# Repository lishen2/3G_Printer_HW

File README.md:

# 3G_Printer_HW
secret project

Standalone not finished, may contain issues use with caution

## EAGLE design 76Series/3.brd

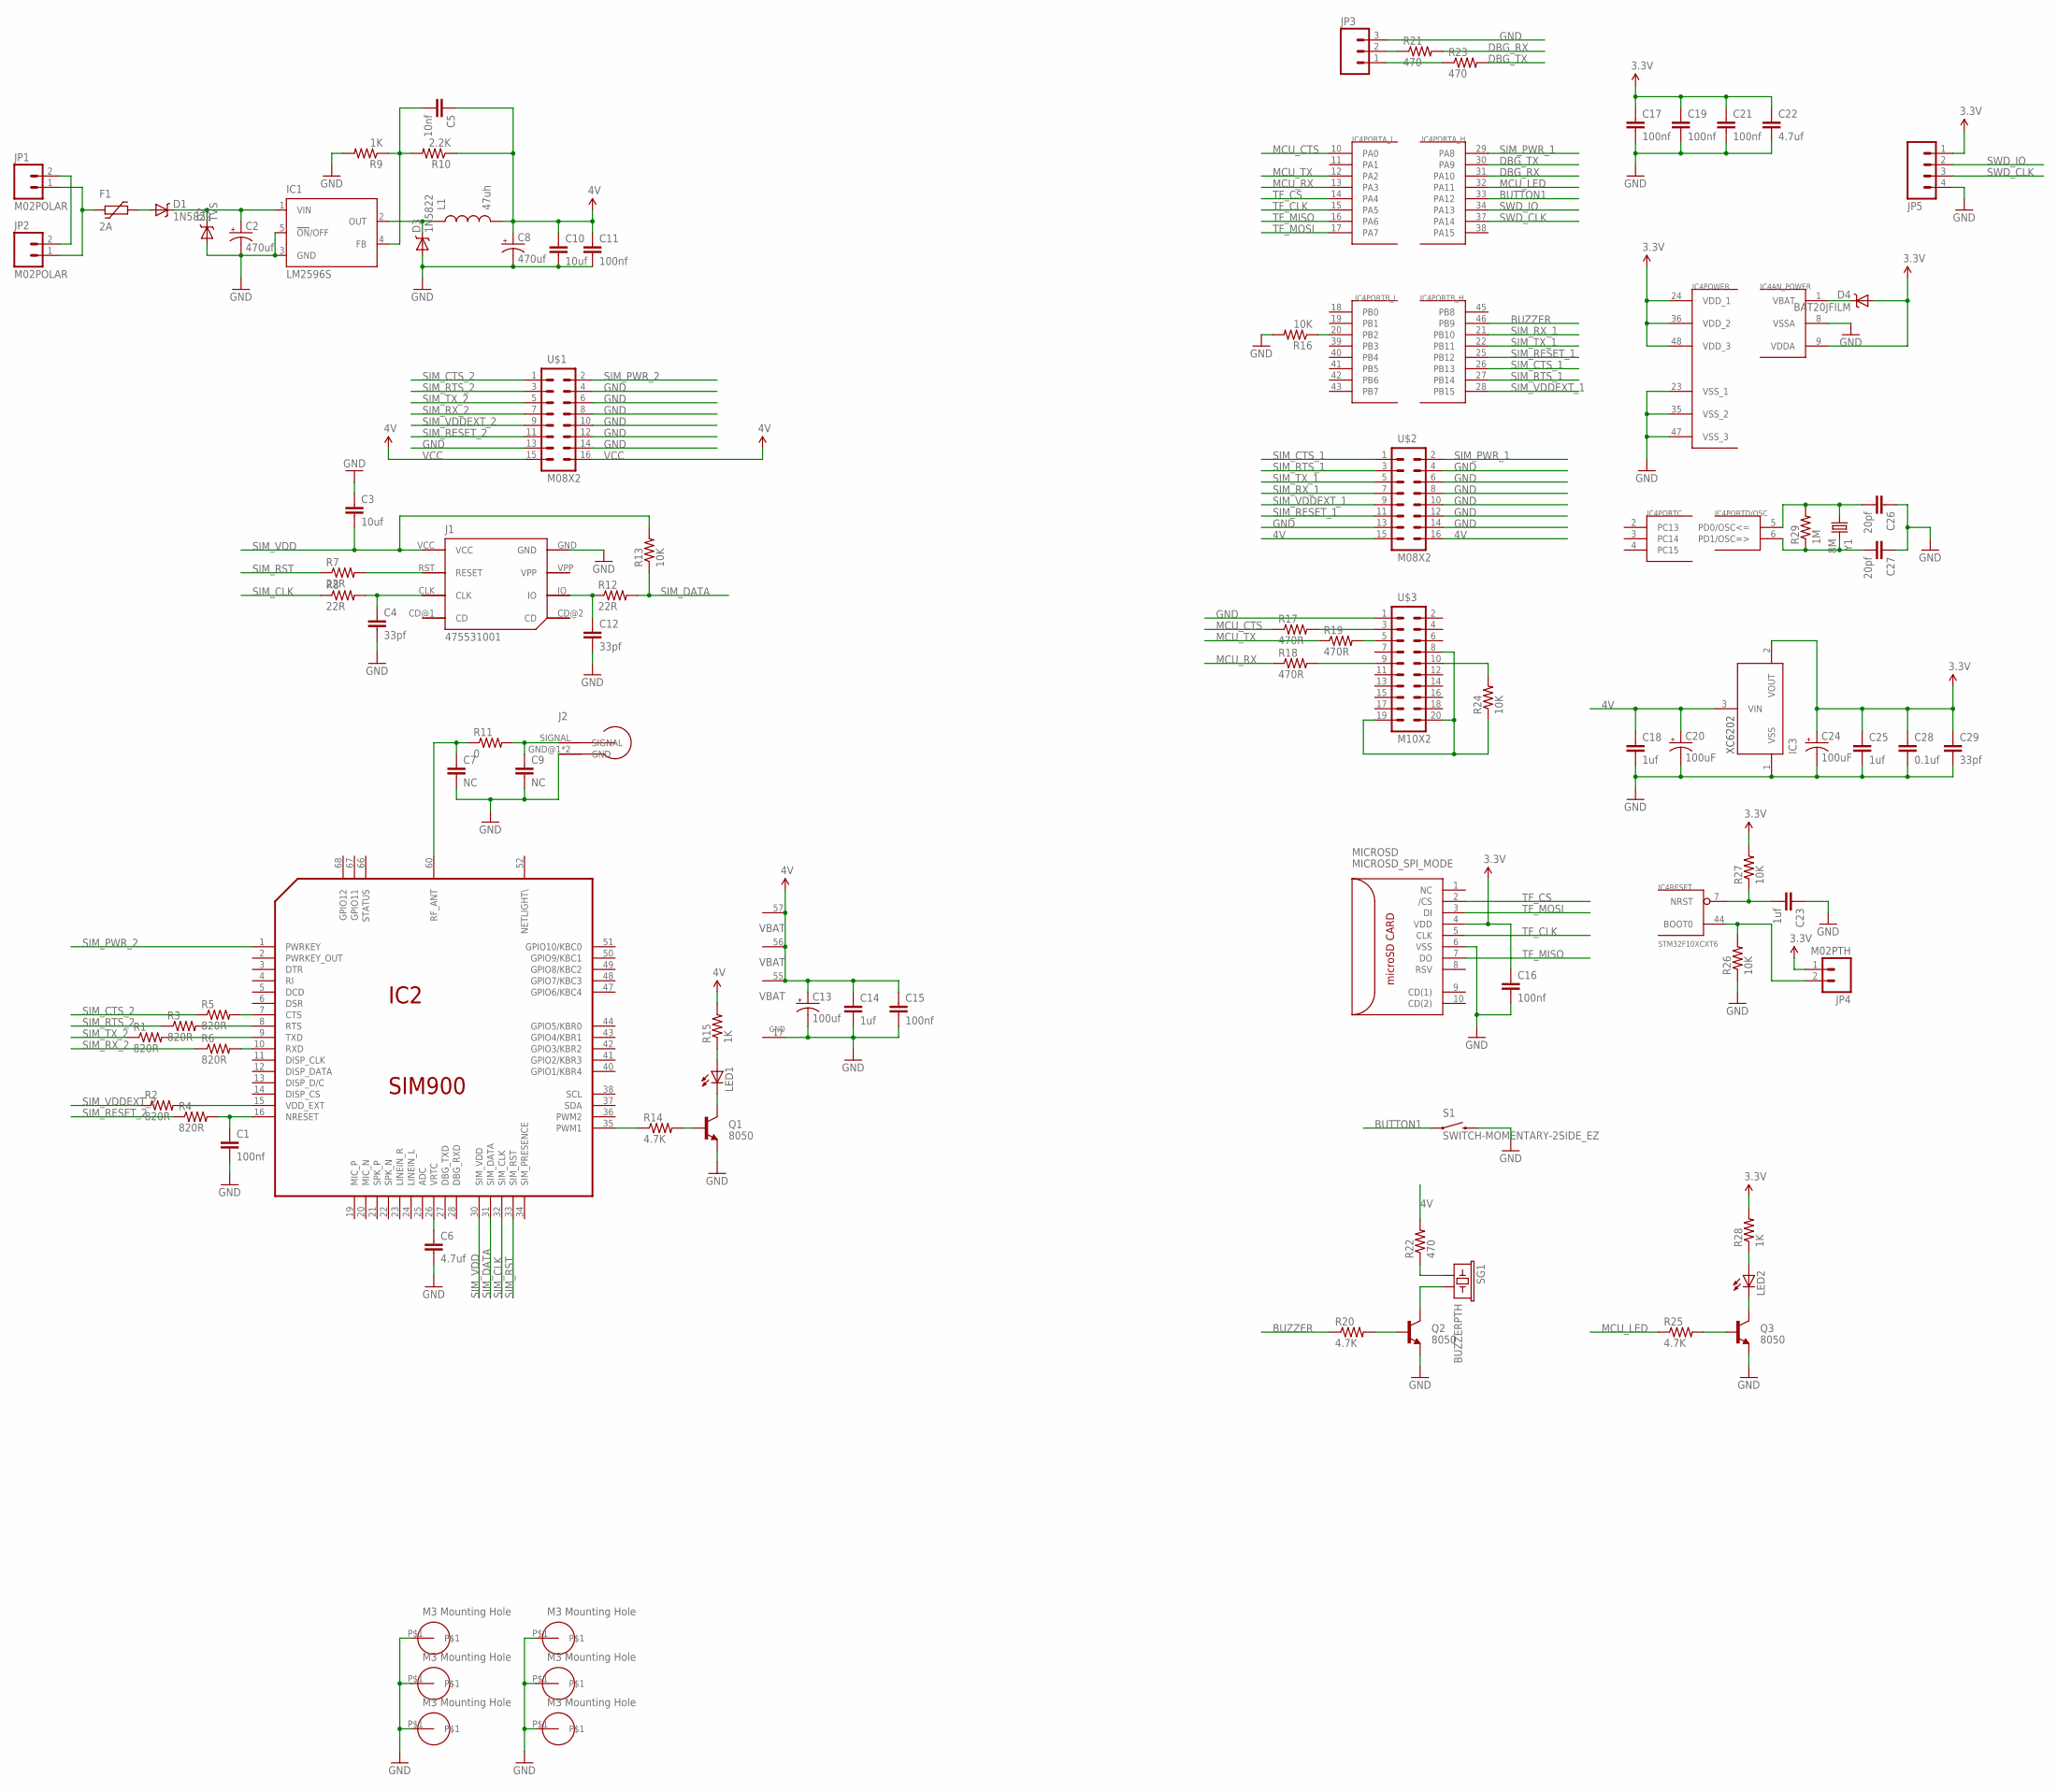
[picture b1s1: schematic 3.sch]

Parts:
C1, C11, C15, C16, C17, C19, C21: 100nf; 0603-CAP
C2: 470uf; CPOL-RADIAL-1000UF-25V
C3, C10: 10uf; 0603-CAP
C4, C12, C29: 33pf; 0603-CAP
C5: 10nf; 0603-CAP
C6, C22: 4.7uf; 0603-CAP
C7, C9: NC; 0603-CAP
C8: 470uf; PANASONIC_G
C13: 100uf; EIA6032
C14, C18, C23, C25: 1uf; 0603-CAP
C20, C24: 100uF; EIA3528
C26, C27: 20pf; 0603-CAP
C28: 0.1uf; 0603-CAP
D1, D3: 1N5822; SMB-DIODE
D2: TVS; SMB-DIODE
D4: BAT20JFILM; SOD-323
F1: 2A; 1812L
IC1: LM2596S; TO263-5
IC2: SIM900
IC3: XC6202; SOT23-3
IC4: STM32F10XCXT6; TQFP48
J1: 475531001
J2: IPEX
JP1, JP2: M02POLAR; MOLEX-1X2
JP3: M03PTH; 1X03
JP4: M02PTH; 1X02
JP5: M04PTH; 1X04
L1: 47uh; IHLP4040DZ
LED1: LEDSML0805; SML0805
LED2: LED3MM
MICROSD: MICROSD_SPI_MODE; MICRO_SD_CONNECTOR
Q1, Q2, Q3: 8050; SOT23
R1, R2, R3, R4, R5, R6: 820R; 0603-RES
R7, R8, R12: 22R; 0603-RES
R9, R15, R28: 1K; 0603-RES
R10: 2.2K; 0603-RES
R11: 0; 0603-RES
R13, R16, R24, R26, R27: 10K; 0603-RES
R14, R20, R25: 4.7K; 0603-RES
R17, R18, R19: 470R; 0603-RES
R21, R22, R23: 470; 0603-RES
R29: 1M; 0603-RES
S1: SWITCH-MOMENTARY-2SIDE_EZ; TACTILE-PTH-SIDEEZ
SG1: BUZZERPTH; BUZZER-12MM
U$1, U$2: M08X2; 2X8
U$3: M10X2; 2X10
U$4, U$5, U$7, U$8, U$10, U$11: M3_MOUNTING_HOLE
Y1: 8M; HC49US

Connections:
3.3V: C16.1, C17.1, C19.1, C21.1, C22.1, C24.A (+), C25.1, C28.1, C29.1, D4.2 (A), IC3.2 (VOUT), IC4.9 (VDDA), IC4.24 (VDD_1), IC4.36 (VDD_2), IC4.48 (VDD_3), JP4.1, JP5.1, MICROSD.4 (VDD), R27.2, R28.2
4V: C18.1, C20.A (+), IC3.3 (VIN), R22.2, U$2.15, U$2.16
BUTTON1: IC4.33 (PA12), S1.1
BUZZER: IC4.46 (PB9), R20.1
DBG_RX: IC4.31 (PA10), R21.2
DBG_TX: IC4.30 (PA9), R23.2
GND: C1.2, C2.2 (-), C3.1, C4.2, C6.2, C7.2, C8.-, C9.2, C10.2, C11.2, C12.2, C13.P$2 (-), C14.2, C15.2, C16.2, C17.2, C18.2, C19.2, C20.C (-), C21.2, C22.2, C23.1, C24.C (-), C25.2, C26.1, C27.1, C28.2, C29.2, D2.A, D3.A, IC1.3 (GND), IC1.5 (!ON!/OFF), IC2.17 (GND), IC2.18 (GND), IC2.29 (GND), IC2.39 (GND), IC2.45 (GND), IC2.46 (GND), IC2.53 (GND), IC2.54 (GND), IC2.58 (GND), IC2.59 (GND), IC2.61 (GND), IC2.62 (GND), IC2.63 (GND), IC2.64 (GND), IC2.65 (GND), IC3.1 (VSS), IC4.8 (VSSA), IC4.23 (VSS_1), IC4.35 (VSS_2), IC4.47 (VSS_3), J1.GND, J2.GND@1 (GND), J2.GND@2 (GND), JP3.3, JP5.4, MICROSD.6 (VSS), Q1.2 (E), Q2.2 (E), Q3.2 (E), R9.2, R16.2, R26.1, S1.2, U$1.4, U$1.6, U$1.8, U$1.10, U$1.12, U$1.13, U$1.14, U$2.4, U$2.6, U$2.8, U$2.10, U$2.12, U$2.13, U$2.14, U$3.1, U$4.P$1, U$5.P$1, U$7.P$1, U$8.P$1, U$10.P$1, U$11.P$1
MCU_CTS: IC4.10 (PA0), R17.1
MCU_LED: IC4.32 (PA11), R25.1
MCU_RX: IC4.13 (PA3), R18.1
MCU_TX: IC4.12 (PA2), R19.1
unnamed: D4.1 (C), IC4.1 (VBAT)
unnamed: C26.2, IC4.5 (PD0/OSC<=), R29.2, Y1.1
unnamed: C27.2, IC4.6 (PD1/OSC=>), R29.1, Y1.2
unnamed: C23.2, IC4.7 (NRST), R27.1
unnamed: IC4.44 (BOOT0), JP4.2, R26.2
unnamed: R24.1, U$3.8, U$3.19, U$3.20
unnamed: JP1.2, JP2.2
unnamed: D3.C, IC1.2 (OUT), L1.P$1 (1)
unnamed: C2.1 (+), D1.C, D2.C, IC1.1 (VIN)
unnamed: F1.P$1 (1), JP1.1, JP2.1
unnamed: C5.2, IC1.4 (FB), R9.1, R10.2
unnamed: R17.2, U$3.3
unnamed: R19.2, U$3.5
unnamed: LED1.C, Q1.3 (C)
unnamed: R24.2, U$3.10
unnamed: C7.1, IC2.60 (RF_ANT), R11.1
unnamed: IC4.20 (PB2), R16.1
unnamed: C9.1, J2.SIGNAL, R11.2
unnamed: D1.A, F1.P$2 (2)
unnamed: IC2.15 (VDD_EXT), R2.2
unnamed: IC2.35 (PWM1), R14.1
unnamed: Q1.1 (B), R14.2
unnamed: LED1.A, R15.1
unnamed: J1.RST (RESET), R7.2
unnamed: C6.1, IC2.26 (VRTC)
unnamed: Q3.1 (B), R25.2
unnamed: C1.1, IC2.16 (NRESET), R4.2
unnamed: IC2.7 (CTS), R5.2
unnamed: IC2.8 (RTS), R3.2
unnamed: IC2.9 (TXD), R1.2
unnamed: C12.1, J1.IO, R12.1
unnamed: IC2.10 (RXD), R6.2
unnamed: JP3.2, R21.1
unnamed: JP3.1, R23.1
unnamed: C4.1, J1.CLK, R8.2
unnamed: Q2.1 (B), R20.2
unnamed: R22.1, SG1.+ (1)
unnamed: Q2.3 (C), SG1.- (2)
unnamed: R18.2, U$3.9
unnamed: LED2.A, R28.1
unnamed: LED2.K (C), Q3.3 (C)
SIM_CLK: IC2.32 (SIM_CLK), R8.1
SIM_CTS_1: IC4.26 (PB13), U$2.1
SIM_CTS_2: R5.1, U$1.1
SIM_DATA: IC2.31 (SIM_DATA), R12.2, R13.1
SIM_PWR_1: IC4.29 (PA8), U$2.2
SIM_PWR_2: IC2.1 (PWRKEY), U$1.2
SIM_RESET_1: IC4.25 (PB12), U$2.11
SIM_RESET_2: R4.1, U$1.11
SIM_RST: IC2.33 (SIM_RST), R7.1
SIM_RTS_1: IC4.27 (PB14), U$2.3
SIM_RTS_2: R3.1, U$1.3
SIM_RX_1: IC4.21 (PB10), U$2.7
SIM_RX_2: R6.1, U$1.7
SIM_TX_1: IC4.22 (PB11), U$2.5
SIM_TX_2: R1.1, U$1.5
SIM_VDD: C3.2, IC2.30 (SIM_VDD), J1.VCC, R13.2
SIM_VDDEXT_1: IC4.28 (PB15), U$2.9
SIM_VDDEXT_2: R2.1, U$1.9
SWD_CLK: IC4.37 (PA14), JP5.3
SWD_IO: IC4.34 (PA13), JP5.2
TF_CLK: IC4.15 (PA5), MICROSD.5 (CLK)
TF_CS: IC4.14 (PA4), MICROSD.2 (/CS)
TF_MISO: IC4.16 (PA6), MICROSD.7 (DO)
TF_MOSI: IC4.17 (PA7), MICROSD.3 (DI)
VCC: C5.1, C8.+, C10.1, C11.1, C13.P$1 (+), C14.1, C15.1, IC2.55 (VBAT), IC2.56 (VBAT), IC2.57 (VBAT), L1.P$2 (2), R10.1, R15.2, U$1.15, U$1.16

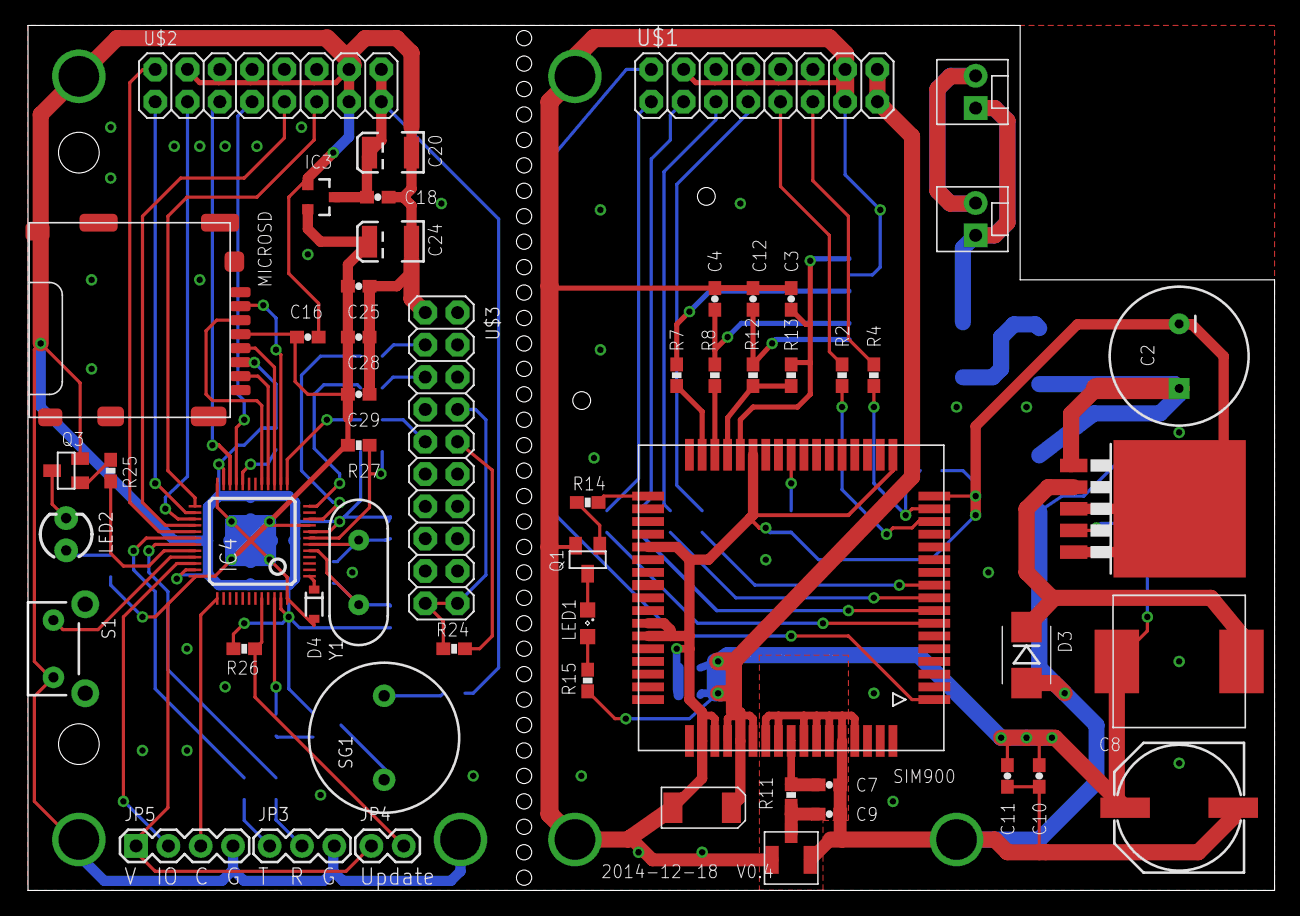
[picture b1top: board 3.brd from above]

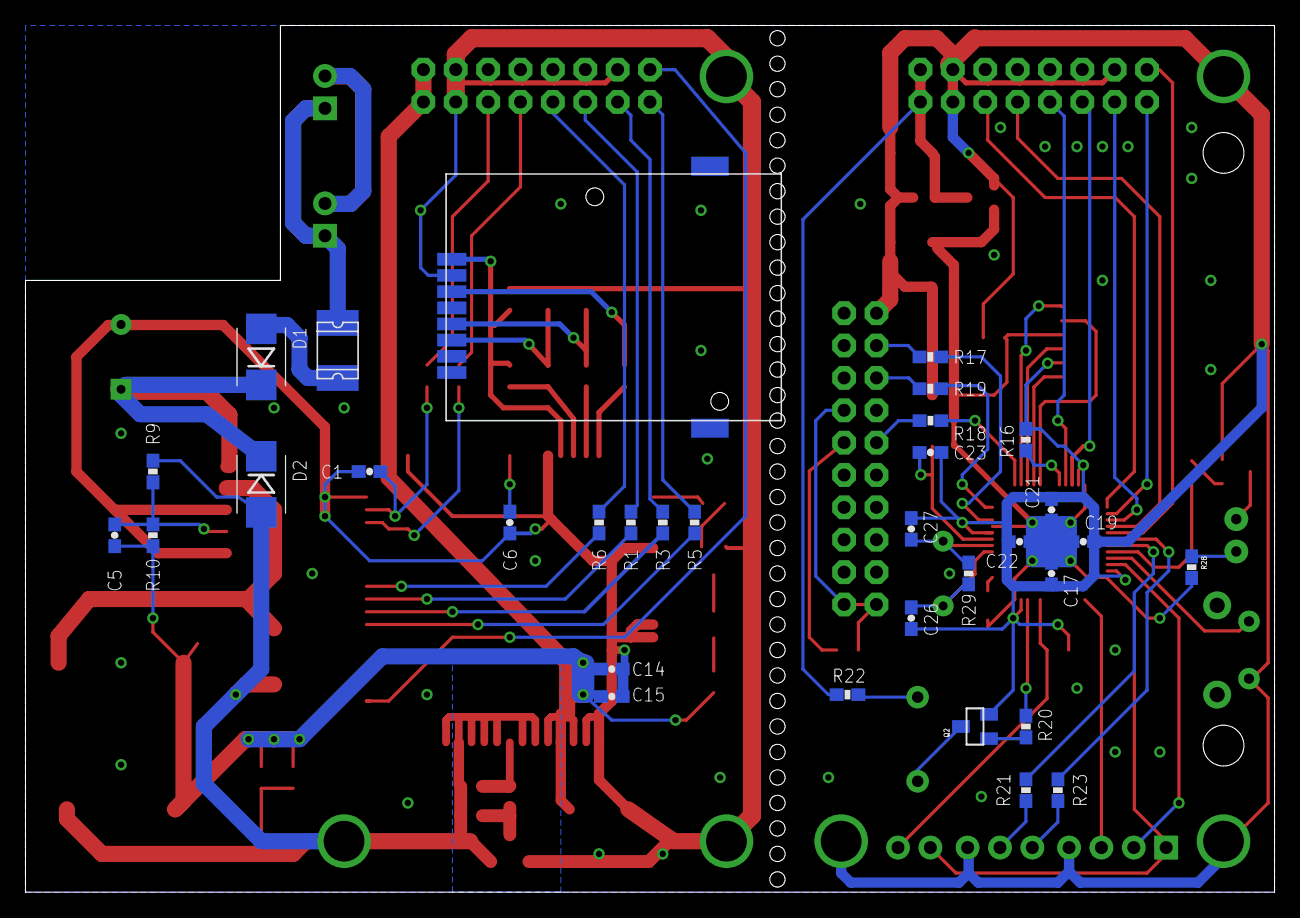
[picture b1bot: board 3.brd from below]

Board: 2 copper layers, 98.0 x 68.0 mm, 93 parts (33 on the bottom side), 77 nets.

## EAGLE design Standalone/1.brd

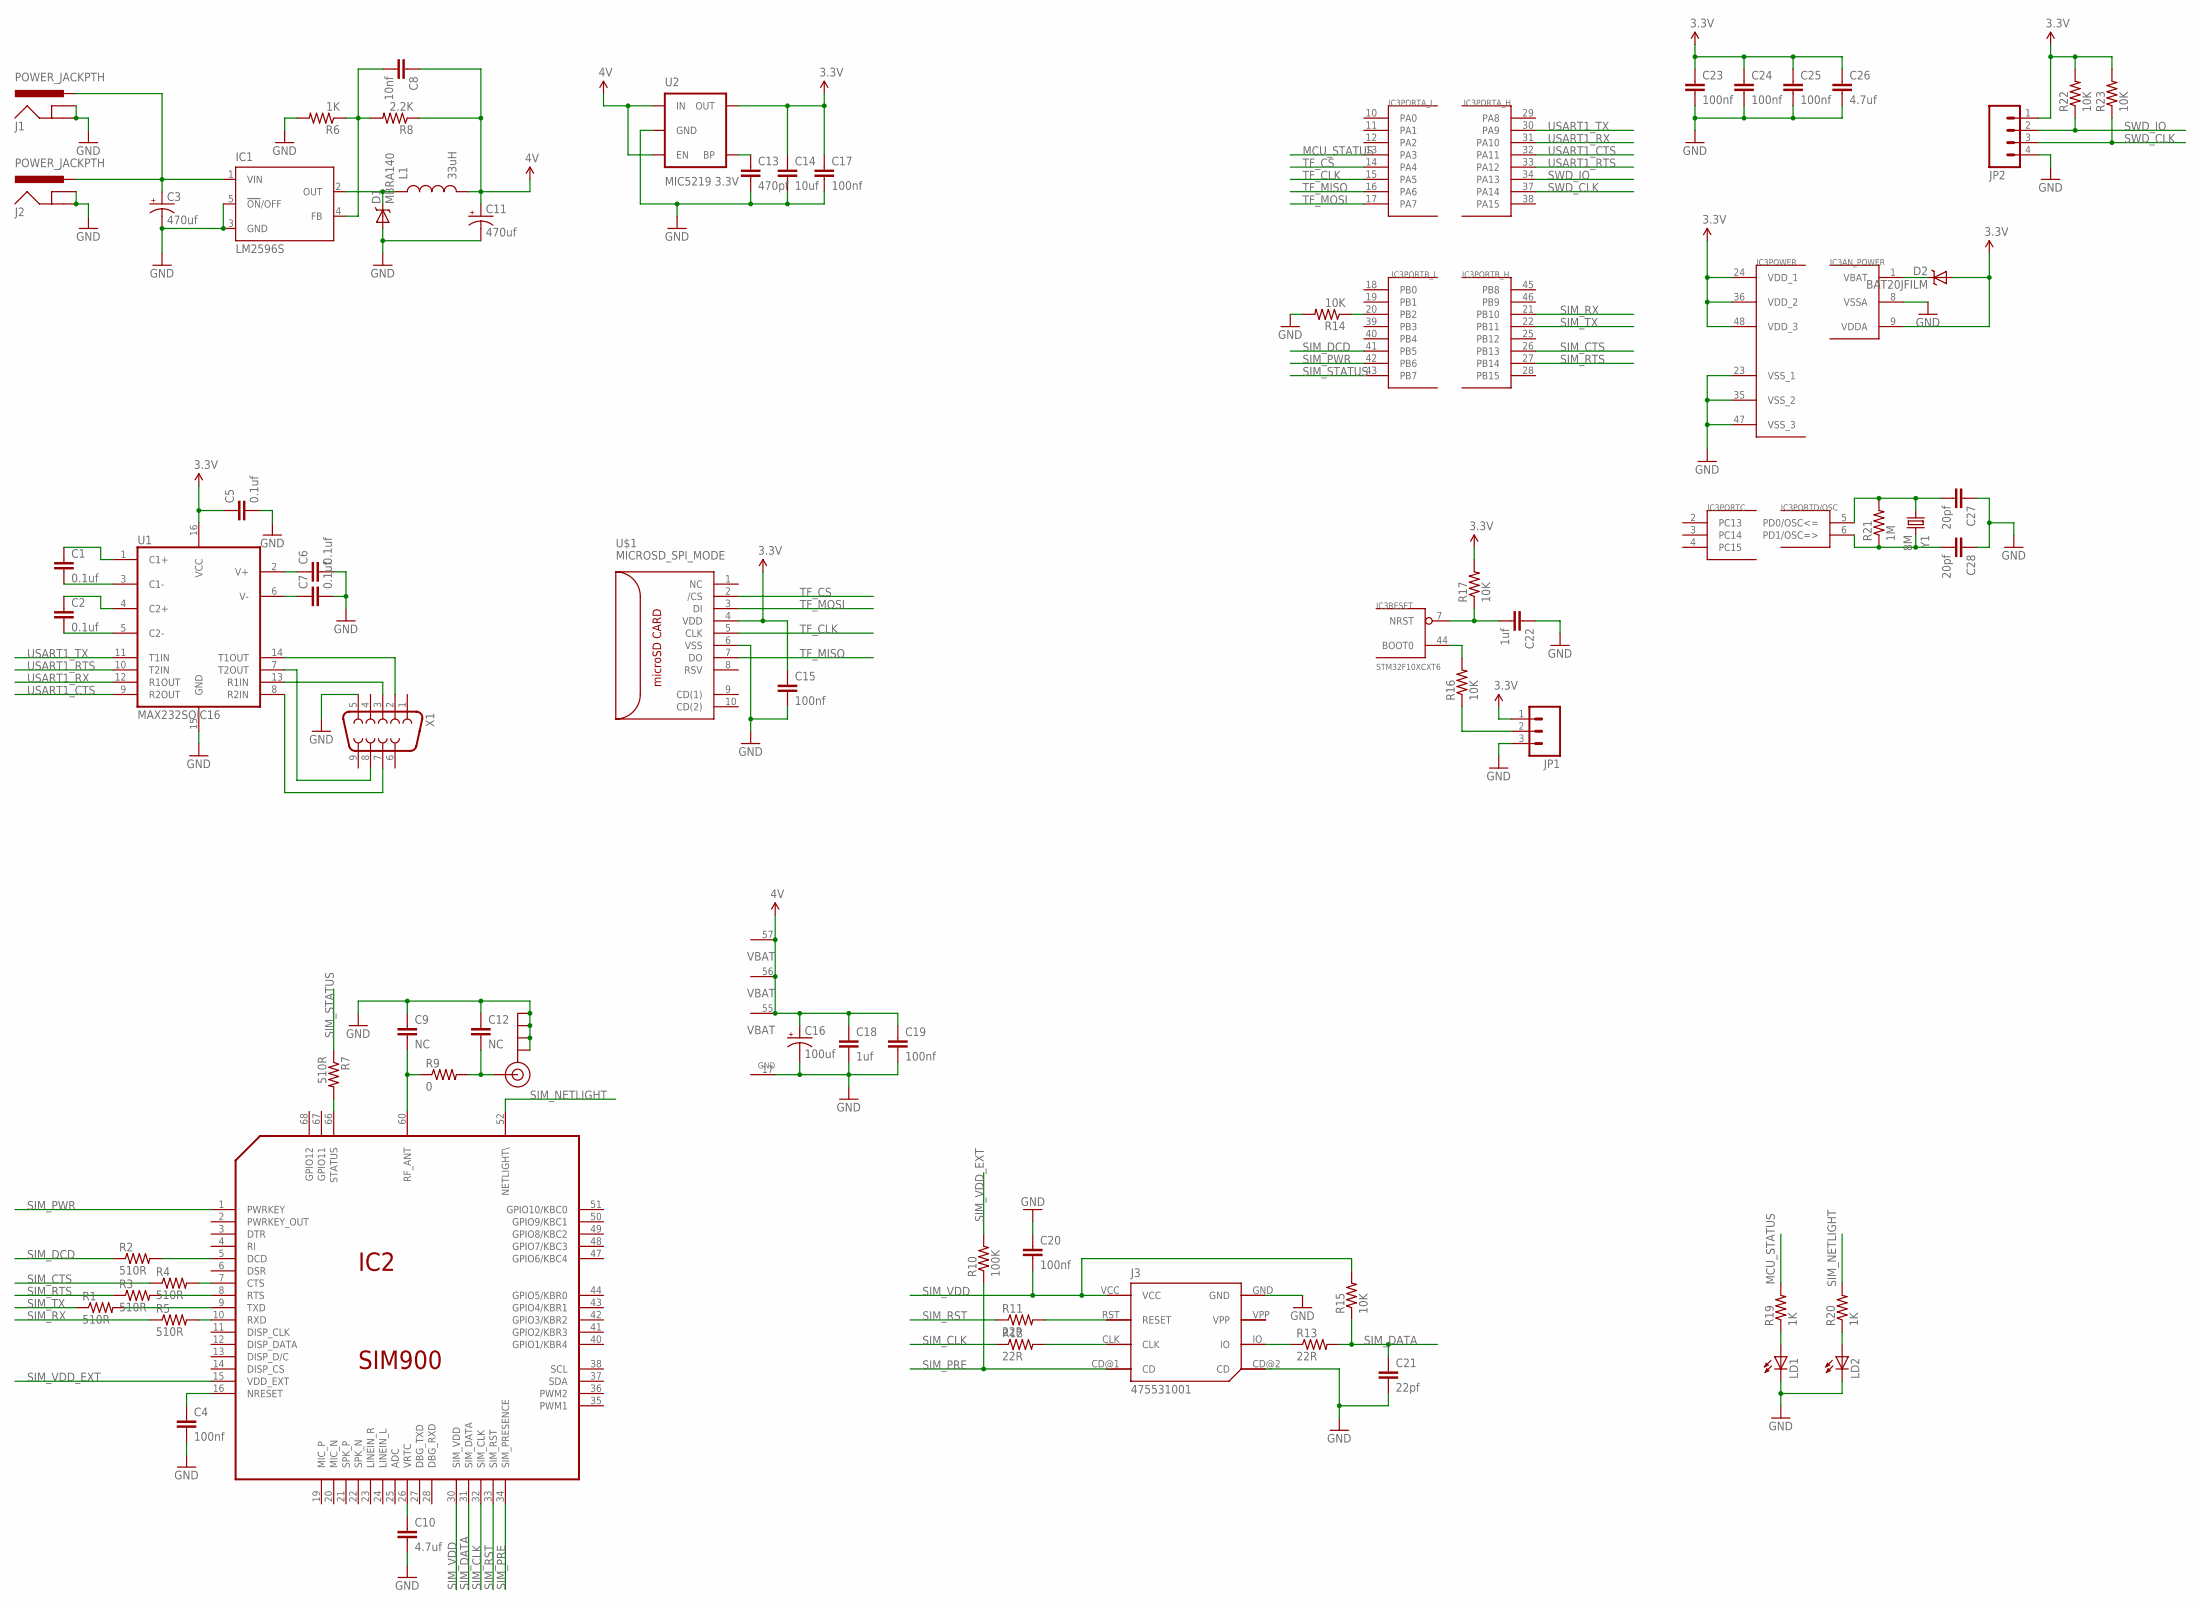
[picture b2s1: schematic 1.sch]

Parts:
C1, C2, C5, C6, C7: 0.1uf; 0603-CAP
C3, C11: 470uf; PANASONIC_G
C4, C15, C17, C19, C20, C23, C24, C25: 100nf; 0603-CAP
C8: 10nf; 0603-CAP
C9, C12: NC; 0603-CAP
C10, C26: 4.7uf; 0603-CAP
C13: 470pf; 0603-CAP
C14: 10uf; 0603-CAP
C16: 100uf; EIA6032
C18, C22: 1uf; 0603-CAP
C21: 22pf; 0603-CAP
C27, C28: 20pf; 0603-CAP
D1: MBRA140; SMA-DIODE
D2: BAT20JFILM; SOD-323
IC1: LM2596S; TO263-5
IC2: SIM900
IC3: STM32F10XCXT6; TQFP48
J1, J2: POWER_JACKPTH; POWER_JACK_PTH
J3: 475531001
J$1: SMA_EDGE; SMA-EDGE
JP1: M03PTH; 1X03
JP2: M04PTH; 1X04
L1: 33uH; CR75
LD1, LD2: LEDCHIP-LED0805; CHIP-LED0805
R1, R2, R3, R4, R5, R7: 510R; 0603-RES
R6, R19, R20: 1K; 0603-RES
R8: 2.2K; 0603-RES
R9: 0; 0603-RES
R10: 100K; 0603-RES
R11, R12, R13: 22R; 0603-RES
R14, R15, R16, R17, R22, R23: 10K; 0603-RES
R21: 1M; 0603-RES
U1: MAX232SOIC16; SO016
U2: MIC5219 3.3V; SOT23-5
U$1: MICROSD_SPI_MODE; MICRO_SD_CONNECTOR
X1: DB9FEMALE; DB9
Y1: 8M; HC49US

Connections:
3.3V: C5.1, C14.1, C15.1, C17.1, C23.1, C24.1, C25.1, C26.1, D2.2 (A), IC3.9 (VDDA), IC3.24 (VDD_1), IC3.36 (VDD_2), IC3.48 (VDD_3), JP1.1, JP2.1, R17.2, R22.2, R23.2, U1.16 (VCC), U2.5 (OUT), U$1.4 (VDD)
GND: C3.-, C4.2, C5.2, C6.2, C7.2, C9.1, C10.2, C11.-, C12.1, C13.2, C14.2, C15.2, C16.P$2 (-), C17.2, C18.2, C19.2, C20.1, C21.2, C22.1, C23.2, C24.2, C25.2, C26.2, C27.1, C28.1, D1.A, IC1.3 (GND), IC1.5 (!ON!/OFF), IC2.17 (GND), IC2.18 (GND), IC2.29 (GND), IC2.39 (GND), IC2.45 (GND), IC2.46 (GND), IC2.53 (GND), IC2.54 (GND), IC2.58 (GND), IC2.59 (GND), IC2.61 (GND), IC2.62 (GND), IC2.63 (GND), IC2.64 (GND), IC2.65 (GND), IC3.8 (VSSA), IC3.23 (VSS_1), IC3.35 (VSS_2), IC3.47 (VSS_3), J1.GND, J1.GNDBREAK, J2.GND, J2.GNDBREAK, J3.CD@2 (CD), J3.GND, J$1.GND@0 (GND), J$1.GND@1 (GND), J$1.GND@2 (GND), J$1.GND@3 (GND), JP1.3, JP2.4, LD1.C, LD2.C, R6.2, R14.2, U1.15 (GND), U2.2 (GND), U$1.6 (VSS), X1.5
MCU_STATUS: IC3.13 (PA3), R19.2
unnamed: D2.1 (C), IC3.1 (VBAT)
unnamed: C27.2, IC3.5 (PD0/OSC<=), R21.2, Y1.1
unnamed: C28.2, IC3.6 (PD1/OSC=>), R21.1, Y1.2
unnamed: C22.2, IC3.7 (NRST), R17.1
unnamed: IC3.44 (BOOT0), R16.2
unnamed: JP1.2, R16.1
unnamed: C3.+, IC1.1 (VIN), J1.PWR, J2.PWR
unnamed: D1.C, IC1.2 (OUT), L1.P$1 (1)
unnamed: C2.2, U1.5 (C2-)
unnamed: C1.2, U1.3 (C1-)
unnamed: C8.2, IC1.4 (FB), R6.1, R8.2
unnamed: C13.1, U2.4 (BP)
unnamed: C1.1, U1.1 (C1+)
unnamed: C2.1, U1.4 (C2+)
unnamed: C6.1, U1.2 (V+)
unnamed: C7.1, U1.6 (V-)
unnamed: IC3.20 (PB2), R14.1
unnamed: U1.13 (R1IN), X1.3
unnamed: U1.14 (T1OUT), X1.2
unnamed: C9.2, IC2.60 (RF_ANT), R9.1
unnamed: C12.2, J$1.SIG (SIGNAL), R9.2
unnamed: U1.7 (T2OUT), X1.8
unnamed: U1.8 (R2IN), X1.7
unnamed: J3.RST (RESET), R11.2
unnamed: C10.1, IC2.26 (VRTC)
unnamed: LD1.A, R19.1
unnamed: LD2.A, R20.1
unnamed: C4.1, IC2.16 (NRESET)
unnamed: IC2.7 (CTS), R4.2
unnamed: IC2.8 (RTS), R3.2
unnamed: IC2.9 (TXD), R1.2
unnamed: J3.IO, R13.1
unnamed: IC2.10 (RXD), R5.2
unnamed: IC2.5 (DCD), R2.2
unnamed: IC2.66 (STATUS), R7.2
unnamed: J3.CLK, R12.2
SIM_CLK: IC2.32 (SIM_CLK), R12.1
SIM_CTS: IC3.26 (PB13), R4.1
SIM_DATA: C21.1, IC2.31 (SIM_DATA), R13.2, R15.1
SIM_DCD: IC3.41 (PB5), R2.1
SIM_NETLIGHT: IC2.52 (NETLIGHT\), R20.2
SIM_PRE: IC2.34 (SIM_PRESENCE), J3.CD@1 (CD), R10.1
SIM_PWR: IC2.1 (PWRKEY), IC3.42 (PB6)
SIM_RST: IC2.33 (SIM_RST), R11.1
SIM_RTS: IC3.27 (PB14), R3.1
SIM_RX: IC3.21 (PB10), R5.1
SIM_STATUS: IC3.43 (PB7), R7.1
SIM_TX: IC3.22 (PB11), R1.1
SIM_VDD: C20.2, IC2.30 (SIM_VDD), J3.VCC, R15.2
SIM_VDD_EXT: IC2.15 (VDD_EXT), R10.2
SWD_CLK: IC3.37 (PA14), JP2.3, R23.1
SWD_IO: IC3.34 (PA13), JP2.2, R22.1
TF_CLK: IC3.15 (PA5), U$1.5 (CLK)
TF_CS: IC3.14 (PA4), U$1.2 (/CS)
TF_MISO: IC3.16 (PA6), U$1.7 (DO)
TF_MOSI: IC3.17 (PA7), U$1.3 (DI)
USART1_CTS: IC3.32 (PA11), U1.9 (R2OUT)
USART1_RTS: IC3.33 (PA12), U1.10 (T2IN)
USART1_RX: IC3.31 (PA10), U1.12 (R1OUT)
USART1_TX: IC3.30 (PA9), U1.11 (T1IN)
VCC: C8.1, C11.+, C16.P$1 (+), C18.1, C19.1, IC2.55 (VBAT), IC2.56 (VBAT), IC2.57 (VBAT), L1.P$2 (2), R8.1, U2.1 (IN), U2.3 (EN)

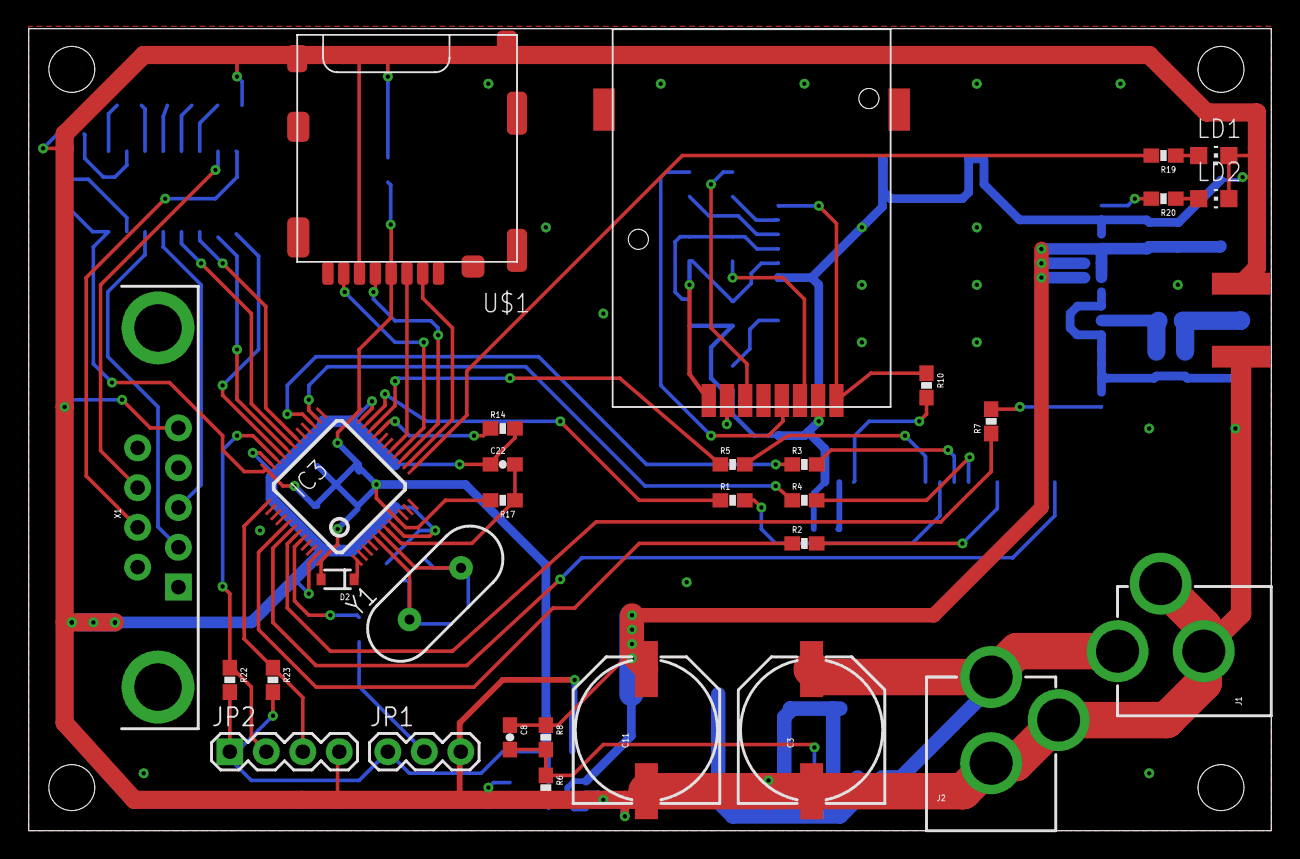
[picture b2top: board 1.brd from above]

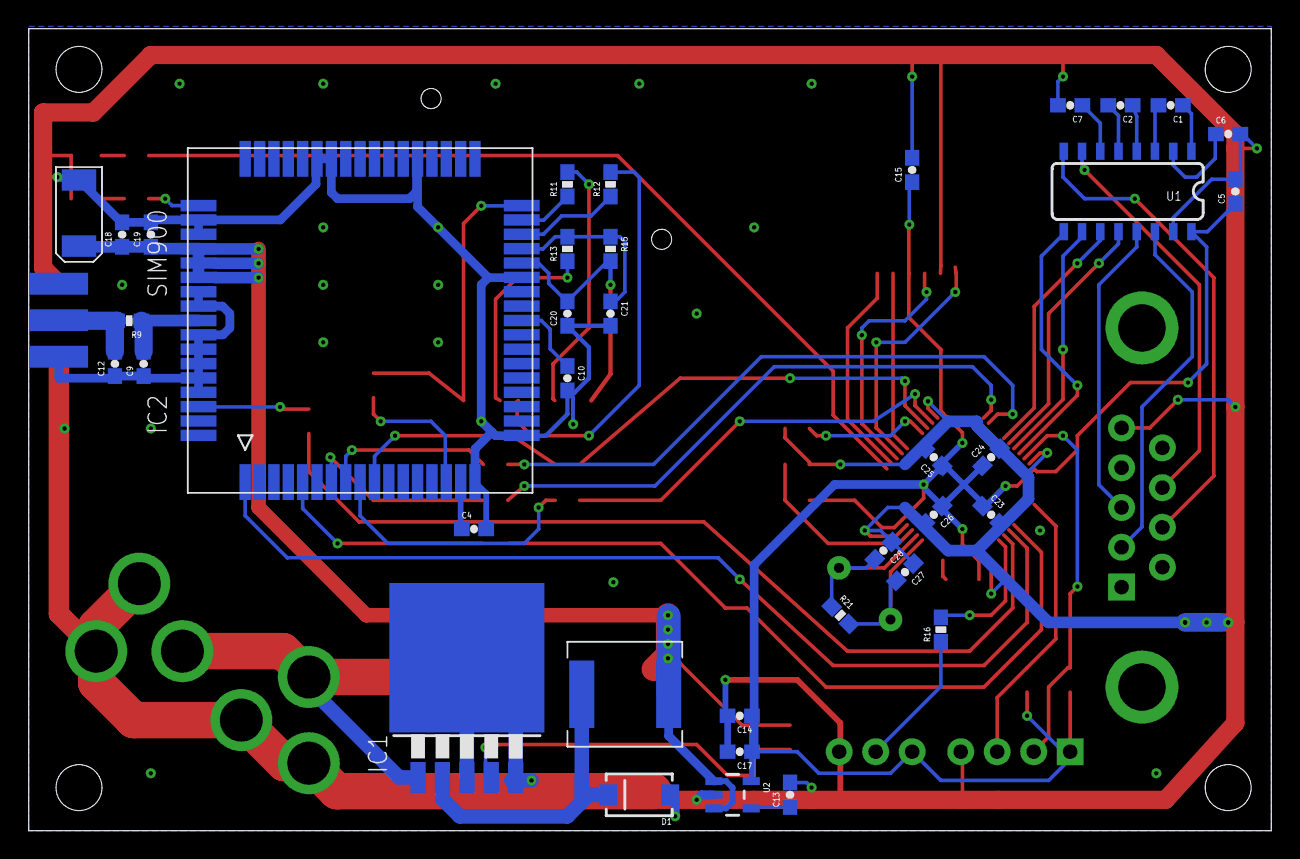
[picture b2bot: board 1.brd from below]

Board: 2 copper layers, 86.5 x 55.8 mm, 69 parts (38 on the bottom side), 64 nets.

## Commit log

2015-07-02 first upload
2015-07-08 modified for model pro5
2015-07-10 update Pro5, minor fixup
2015-07-12 first test board version
2018-11-09 upload unencrypt file

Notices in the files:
parts and their libraries:
SparkFun-Connectors: Licensing: CC v3.0 Share-Alike You are welcome to use this library for commercial purposes.
